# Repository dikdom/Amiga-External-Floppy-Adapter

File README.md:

# Amiga external floppy adapter mod
This rev2.1 mod allows the user to select if the external drive shall be DF1 or DF2.
This external adapter also makes it possible to use them in pair: one for DF1 and one for DF2. Unfortunately Retro Ninja's adapter was lacking 
this feature (despite the passthrough connector - RN's adapter allowed only DF1..)

The TH components were replaced with SMD for saving PCB space. The unused inputs of the logical ICs are tied to ground or +5V, so there is no 
floating inputs and outputs.
Also with this revision it is possible that no SMD component is needed if the adapter is used only with a Gotek drive (only ext floppy 
DSUB23 connector, power and floppy socket needs to be soldered).

The PCB is preconfigured: the Gotek option (no SMD) and DF1 drive is selected.

Detected issues:
- DF1 is not routed to the passthrough connector, so in case of two drive configuration it is not possible to configure the second drive to DF1
- Power cord is twisted while connected to the drives, so order of the pins should be reversed
- 24 pin pinheader socket for the passthrough cable is very hard to find, this should be replaced with a 26 pin header, but see future plans...
- Couldn't find straight floppy power connector and didn't want to mount a simple 1x4 pinheader (I wanted to avoid the accidental reverse 
connection), so I soldered the power cable directly to the PCB. That is also not safe as the cable can break after a few bending. (I used hotglue
to protect cable from bending and breaking - but that is pretty ugly).
- 74LS00 is not open collector output logic, so having two of these modules fully populated with SMDs is probably not a good idea. 72LS00(74HCT00) should be replaced
with a 74LS03 (same pinout, opencollector output). THIS NEEDS TO BE TESTED!

Other plans for the future:
- I would remove the passthrough connector and attach a simple second floppy connector for DF2. I guess there are enough logical gates available for DF2 onboard.

# Retro Ninja Amiga external floppy adapter
An adapter that allows external connection of Shugart floppy disk drive (in theory) or Gotek drives (tested)

This is work in progress and the first revision of the board is just a proof of concept. It has only been tested with a Gotek USB emulator.
It was designed to plug directly into the external floppy port of the Amiga and connect a Gotek USB emulator with a 34-pin IDC cable and a power cable. The floppy connector on the board is rotated so a floppy cable can go in a straight loop to a Gotek laying on top of the Amiga.
It should also be possible to mount the adapter in an external case but the floppy cable would have to be turned 180 degrees to match the connectors of the board and a Gotek. It would be pretty hard to fit a floppy power connector inside a case using the current design but the power cables could be soldered directly to the board.

J1 is the male 23 pin D-sub connector that plugs into the external drive port on the amiga. Pretty hard to find these today but it looks like new ones will be manufactured soon.

J2 is a male header for connecting the floppy cable. Connector can be straight or right angle, open or walled depending on what you got and what you want.

J3 is for floppy power connector. Cables can be soldered directly to board if needed.

J4 is the passthrough connector for a second or third external drive.
Connect first row of pins on header (1...23) to first row of pins on female D-sub (1...12).
Connect second row of pins on header (2...22) to the second row of pins on female D-sub (13...23). **Warning!** I have not tested this functionality yet as I don't have a female 23-pin D-sub. Try at your own risk.

This design was based on information gathered from Amiga System Programmer's Guide by Abacus and from the scematics for the A1020 drive.
Designed with Fusion 360. Gerber files and Eagle schematics included.

## BOM
 |Component|Pcs |Name|Comment|
 |:--------|---:|:---|:------|
 | 74LS00 | 1 | IC1 | 74HCT00 works fine |
 | 74LS74 | 1 | IC2 | 74HCT74 works fine | 
 | 100nF ceramic capacitor | 2 | C1, C2 ||
 | 1k resistor | 4 | R1, R2, R3, R4 ||
 | 12k resistor | 1 | R5 ||
 | D-sub 23M connector | 1 | J1 | D-sub This connector is pretty hard to source at the moment. Try eBay |
 | 34-pin male header | 1 | J2 | 2x17 pin 2.54mm pitch. For floppy cable IDC connector |
 | 4 pin header | 1 | J3 | 2.54mm pitch. For floppy power cable connector (or solder cables directly to board) |
 | 24-pin header | 1 | J4 | 2x12 pin 2.54mm pitch header for outgoing connection to next drive in chain. For example IDC to DB23F. D-sub 23F connectors were manufactured by Unicorns and can't be found today |

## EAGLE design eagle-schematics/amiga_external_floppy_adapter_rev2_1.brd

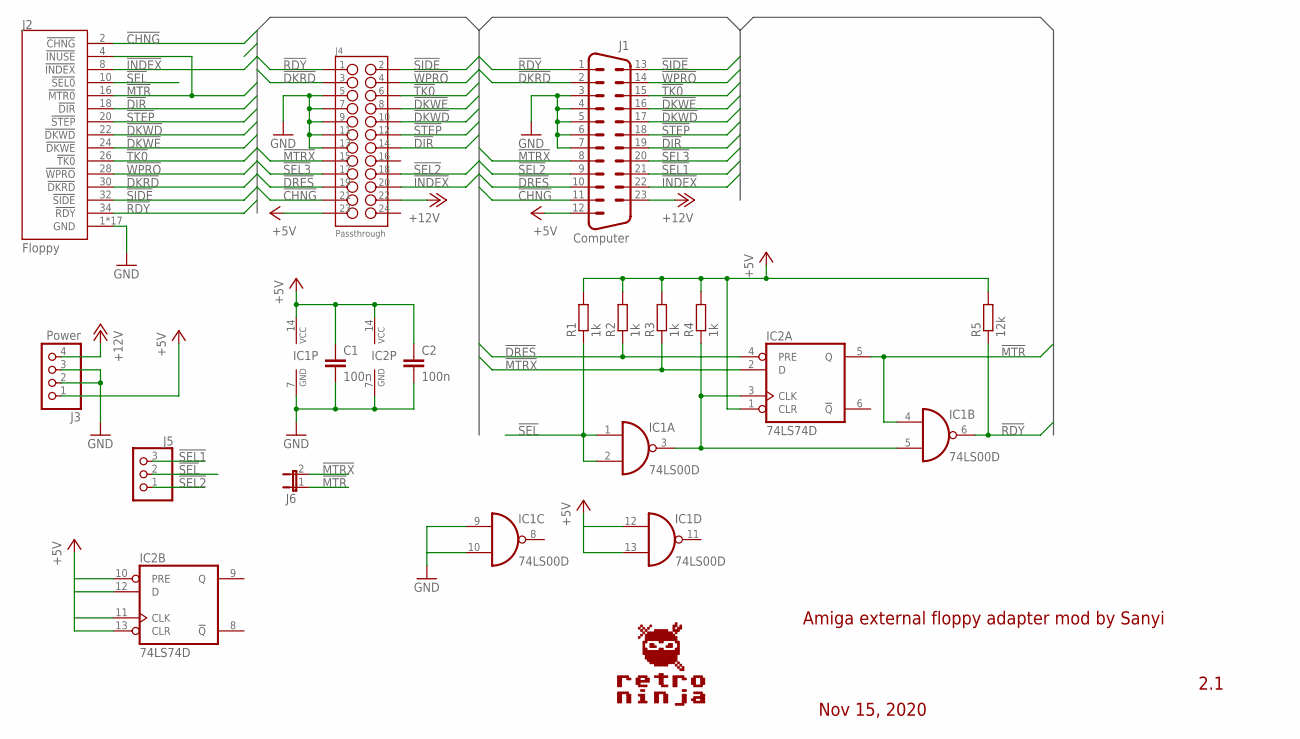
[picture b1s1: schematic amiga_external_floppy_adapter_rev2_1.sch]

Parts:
C1, C2: 100n; C1206
IC1: 74LS00D; SO14
IC2: 74LS74D; SO14
J1: Computer; DSUB_M23D
J2: Floppy; HEADER_2X17_WALLED
J3: Power; 1X04
J4: Passthrough; HEADER_2X12_WALLED
J5: PINHD-1X3; 1X03
J6: JP1E; JP1
R1, R2, R3, R4: 1k; R1206
R5: 12k; R1206

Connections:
!CHNG: J1.11, J2.2 (!CHNG), J4.21
!DIR: J1.19, J2.18 (!DIR), J4.14
!DKRD: J1.2, J2.30 (!DKRD), J4.3
!DKWD: J1.17, J2.22 (!DKWD), J4.10
!DKWE: J1.16, J2.24 (!DKWE), J4.8
!DRES: IC2.4 (PRE), J1.10, J4.19, R2.1
!INDEX: J1.22, J2.8 (!INDEX), J4.20
!MTR: IC1.4 (I0), IC2.5 (Q), J2.4 (!INUSE), J2.16 (!MTR0), J6.1
!MTRX: IC2.2 (D), J1.8, J4.15, J6.2, R3.1
!RDY: IC1.6 (O), J1.1, J2.34 (!RDY), J4.1, R5.1
!SEL: IC1.1 (I0), IC1.2 (I1), J2.10 (!SEL0), J5.2, R1.1
!SEL1: J1.21, J5.3
!SEL2: J1.9, J4.18, J5.1
!SEL3: J1.20, J4.17
!SIDE: J1.13, J2.32 (!SIDE), J4.2
!STEP: J1.18, J2.20 (!STEP), J4.12
!TK0: J1.15, J2.26 (!TK0), J4.6
!WPRO: J1.14, J2.28 (!WPRO), J4.4
+5V: C1.1, C2.1, IC1.12 (I0), IC1.13 (I1), IC1.14 (VCC), IC2.1 (CLR), IC2.10 (PRE), IC2.11 (CLK), IC2.12 (D), IC2.13 (CLR), IC2.14 (VCC), J1.12, J3.1, J4.23, R1.2, R2.2, R3.2, R4.2, R5.2
+12V: J1.23, J3.4, J4.22
GND: C1.2, C2.2, IC1.7 (GND), IC1.9 (I0), IC1.10 (I1), IC2.7 (GND), J1.3, J1.4, J1.5, J1.6, J1.7, J2.1 (GND), J2.3 (GND), J2.5 (GND), J2.7 (GND), J2.9 (GND), J2.11 (GND), J2.13 (GND), J2.15 (GND), J2.17 (GND), J2.19 (GND), J2.21 (GND), J2.23 (GND), J2.25 (GND), J2.27 (GND), J2.29 (GND), J2.31 (GND), J2.33 (GND), J3.2, J3.3, J4.5, J4.7, J4.9, J4.11, J4.13
unnamed: IC1.3 (O), IC1.5 (I1), IC2.3 (CLK), R4.1

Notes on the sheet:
2.1
Nov 15, 2020
Amiga external floppy adapter mod by Sanyi

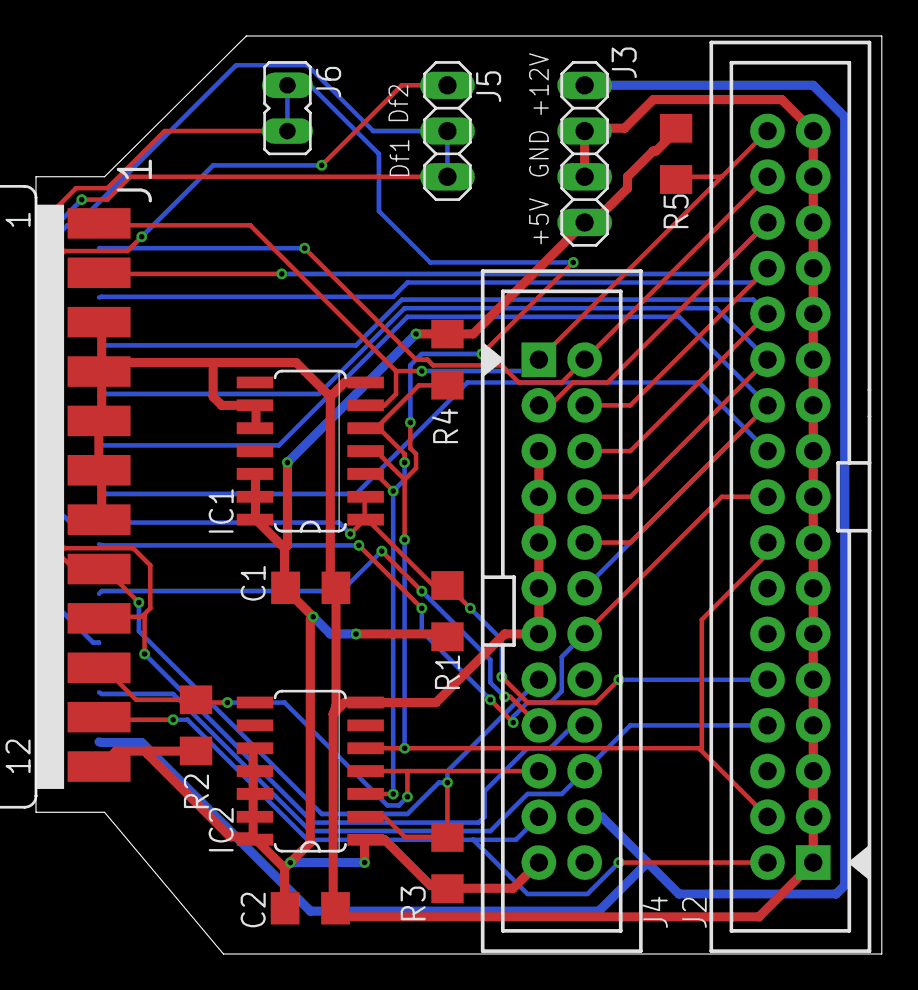
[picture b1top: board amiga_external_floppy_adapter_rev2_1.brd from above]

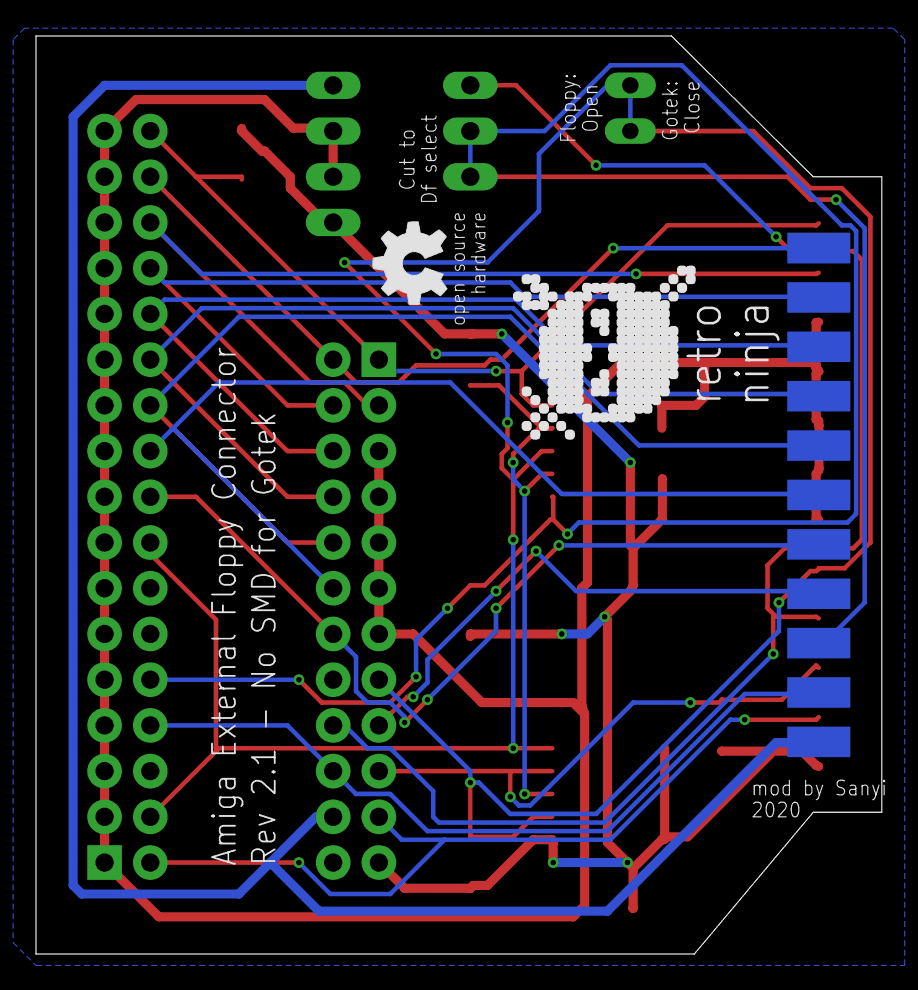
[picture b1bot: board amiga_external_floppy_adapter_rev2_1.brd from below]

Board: 2 copper layers, 47.0 x 51.0 mm, 17 parts (2 on the bottom side), 22 nets.

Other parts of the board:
U$1: RETRONINJA_NOTEXT_10MM
U$2: OSHW_5MM

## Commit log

2020-11-15 Update README.md
    General description of the mod
2020-11-16 Files for rev2.1 are updated/added, readme file modified slightly
2020-11-16 Update README.md
    image name fixed
2020-11-16 Update README.md
    readme
2020-11-19 Update README.md
    Comment about 74LS00
